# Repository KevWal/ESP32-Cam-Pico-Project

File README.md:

ESP32 Camera Tracker
Written to run on ESP32-Cam board + Lora + GPS

Original code by mkshrps - https://github.com/mkshrps/espcam
Some other ideas from Stuart - https://stuartsprojects.github.io/2020/08/27/ESP32CAM-TrackerAddOn-Board.html

1. Transmits jpg data over lora using SSDV protocol;
2. Interleaves GPS using UKHAS protocol packets;
3. Compatible with PITS LoRa-Gateway receiver.

ESP32-CAM board does not include lora device or GPS device which need to be connected.

Program through the U0R and U0T pins (serial pins) with GPIO0 connected to Gnd.
Debugging output is also on the U0R and U0T pins.

Weights
------
12.4g - Tracker inc 180deg Camera, guitar wire GPS & LoRa Aerial<br>
25g - 3 x AAA soldered together with wire - lasted 14 hours in freezer<br>
21g - 2 x AAA in holder with wire<br>
40g - 2 x AA in holder with wire<br>
14g - 450Ma LiPo<br>

LiPo Version, 26.5g total weight:<br>
1 x Qualtex, 72Ltr Helium, 10g free lift, 0.120m3 unstretched volume, 6,400m burst, 1.7m/sec ascent, 60 mins to burst<br>
2 x Qualtex, 58Ltr Helium each, 10g free lift each, 0.120m3 unstretched volume, 8,400m burst, 1.9m/sec ascent, 75 mins to burst<br>

AA Version, 52.5g total weight:<br>
1 x 100g Pawan, 200ltr Helium, 50g free lift, 20,325m burst, 2.9m/sec ascent, 117mins to burst

AAA Version, 12.5g + 25g = 38g total weight:<br>
1 x Qualtex, 70Ltr Helium, 10g free lift, 0.120m3 unstretched volume, 4,900m burst, 1.7m/sec ascent, 48 mins to burst<br>
2 x Qualtex, 62Ltr Helium each, 10g free lift each, 0.120m3 unstretched volume, 7,500m burst, 1.9m/sec ascent, 65 mins to burst<br>
2 x Chineese, 58Ltr Helium each, 6g free lift each, 0.120m3 unstretched volume, 7,640m burst, 1.9m/sec ascent, 65 mins to float!  42g / 2 = 21g each + 6g = 27g each

Buck version intended for LiPo but used for 3 x AAA

PCB
---

The PCB is designed with many options, mainly around power.  The board is designed to be powered by 2 x AAA or a 3.7v Lipo.  With 2 x AAA I found it needs a boost converter if using the ATGM GPS.  With 1 x 3.7v Lipo I recomend using the buck convertor.  You could use the 3.3v limiting effect of the Boost regulator, but as it is a charge doubler style is uses more current from the battery.

*Flying showed 3 x AAA with a buck convertor is a good option.*

GPS
---
Expects a NMEA GPS, tested with ATGM and UBLOX MAX GPS's

Lora
----
PCB is based on a Dorji DRF1278F LORA module.

Code should support any of the LORA modules listed here:
https://github.com/sandeepmistry/arduino-LoRa

Cameras
-------
Tested with various view angle versions of the OV2640.  This is the standard ESP32 camera.

Some research on other options below.

OV2640 - 1/4" color CMOS UXGA (1600x1200) 2 megapixel image sensor
Used XGA = 1024x768 or VGA = 640x480
https://www.uctronics.com/download/cam_module/OV2640DS.pdf

OV3660 - 3 megapixels
Supports up to FRAMESIZE_QXGA (2048x1536)
https://github.com/espressif/esp32-camera/files/3783752/OV3660_CSP3_DS_1.3_sida.pdf

OV5640 - 1/4" color CMOS QSXGA 5 megapixel image sensor
Supports up to FRAMESIZE_QSXGA (2560x1920)
https://www.uctronics.com/download/Image_Sensor/OV5640_CSP3_DS.pdf

OV7670 - 0.3Mp
Not reasearched due only 0.3Mp!

OV7725 - 
Supports up to FRAMESIZE_VGA (640x480), doesnt support JPEG

OV9650 - Not supported in main repo.
https://www.uctronics.com/index.php/ov9650-13-mega-pixels-camera-module-p-817l.html

NT99141
Supports QVGA (320x240 xskip or crop), VGA(640x480 xskip or crop) and HD (1280x720)

https://github.com/espressif/esp32-camera/tree/master/sensors
Included on github latest:
	#define OV2640_PID     (0x26)
	#define OV3660_PID     (0x36)
	#define OV5640_PID     (0x56)
	#define OV7670_PID     (0x76)
	#define OV7725_PID     (0x77)
	#define OV9650_PID     (0x96)
	#define NT99141_PID     (0x14)

Included in esp32 v1.04:
	#define OV2640_PID     (0x26)
	#define OV3660_PID     (0x36)
	#define OV7725_PID     (0x77)
	#define OV9650_PID     (0x96)

ESP32 Cam module
----------------
https://randomnerdtutorials.com/esp32-cam-ai-thinker-pinout/<br>
https://docs.ai-thinker.com/esp32-cam<br>
https://docs.ai-thinker.com/_media/esp32/docs/esp32_cam_sch.pdf<br>
https://www.espressif.com/sites/default/files/documentation/esp32_technical_reference_manual_en.pdf<br>
https://github.com/espressif/esptool/wiki/ESP32-Boot-Mode-Selection

GPIO32 controls camera power, but if you power the camera down I cant seem to re-initialise it without a reboot (which is now done through a deep sleep reboot)

Arduino IDE
-----------
I added a custom board definition for esp32camkw.upload.speed=921600 to speed uploads.
C:\Users\WALTONK\AppData\Local\Arduino15\packages\esp32\hardware\esp32\1.0.4

Simple Build Notes  - 3 x AA/AAA option
---------------------------------------
Batteries - 3 x AA/AAA = 4.8v down to 2.4v

Reg - MCP170333MB SOT89 or similar<br>
Reg - Add C8, C10, C11 & C12 capacitors

GPS - Tested with ATGM or UBlox Max 3.3v GPS chips<br>
GPS - Add GPS Ferrites and capacitors

Tx - Add Dorji DRF1278F module<br>
Tx - Add R1, C7, C3 and C6<br>
Tx - Set jumper to 3.3v

ESP32 - Add C2, C5, R5 & R6<br>
ESP32 - Remove ESP32 Regulator and Flash transistor<br>
ESP32 - Add ESP32 Camera module to PCB

GPS Antenna - Add chip antenna or 46mm wire (total length)<br>
LoRa Antenna - Add 185mm wire (total length)

Lora Mode
---------
Code setup for:
	Implicit Header (LoRa.beginPacket(1))
	SpreadingFactor(6);
    SignalBandwidth(20.8E3);
    ErrorCodingRate4(5);
    SyncWord(0x12);
    enableCrc();
= Dave Akerman PITS mode 1
https://github.com/PiInTheSky/lora-gateway

Power Consumption
------------------
ESP32 Cam module with regulator removed and flash LED transistor removed<br>
	44ma - Default frequency<br>
	14ma - Reduce to 20Mhz<br>
	14ma - Turn off BT & WIFI<br>
	16ma - Post SPI / Lora Setup<br>
	42ma - Camera setup<br>
	38ma - Disable camera XCLK<br>
	15ma - Turn off camera
	
Board Power Consumption by Frequency, with Lora, GPS and Camera attached but not initialised
	160Mhz, 55ma, 80Mhz, 48ma
	40Mhz, 38ma, 30Mhz, 38ma
	20Mhz, 36ma, 10Mhz, 35ma
	8Mhz, 34ma, 4Mhz, 34ma
	2Mhz, 34ma, 1Mhz, 34ma

ToDo
----
See if we can get Lora and SD Card working together, event though they share pins.  
Stuart did here, but didnt send images: 
https://stuartsprojects.github.io/2020/08/07/ESP32CAM-as-a-Balloon-Tracker-Really!-Copy.html
https://stuartsprojects.github.io/2020/08/27/ESP32CAM-TrackerAddOn-Board.html

Send packets multiple times or auto request resends?

RTTY Code
	Lora library currently in use doesn't appear to have RTTY mode options
	https://github.com/sandeepmistry/arduino-LoRa/blob/master/src/LoRa.cpp
	PITS FSK / RTTY mode details here:
		https://github.com/PiInTheSky/pits/commit/30943ab8ea988695e4e158648f1855fd9fa906bd
		http://www.daveakerman.com/?p=2350
	Stuarts RTTY option here:
		https://github.com/StuartsProjects/Tracker-Library/blob/master/FSK_RTTY2.h
		https://github.com/StuartsProjects/Tracker-Library/blob/master/FSK_RTTY3.h

Add Lora calling frequency tx.

Add use of HabPack binary protocol

Report gps signal quality?
	Base on https://github.com/mikalhart/TinyGPSPlus/blob/master/examples/SatelliteTracker/SatelliteTracker.ino

Record Voltage when taking a picture and send it next telem packet.

PCB
---
Move reset switch hole to be slightly more aligned

Thinner middle pad for buck reg to allow different footprint

Vsupply resister divider on another adc pin too, no solder jumper neeeded.

Increase PCB string holes size, and 4 corner holes to allow vertical down suspension

Lengthen PCB

Different boost converter - current uses lots of current and can't supply enough output current when batteries weak.

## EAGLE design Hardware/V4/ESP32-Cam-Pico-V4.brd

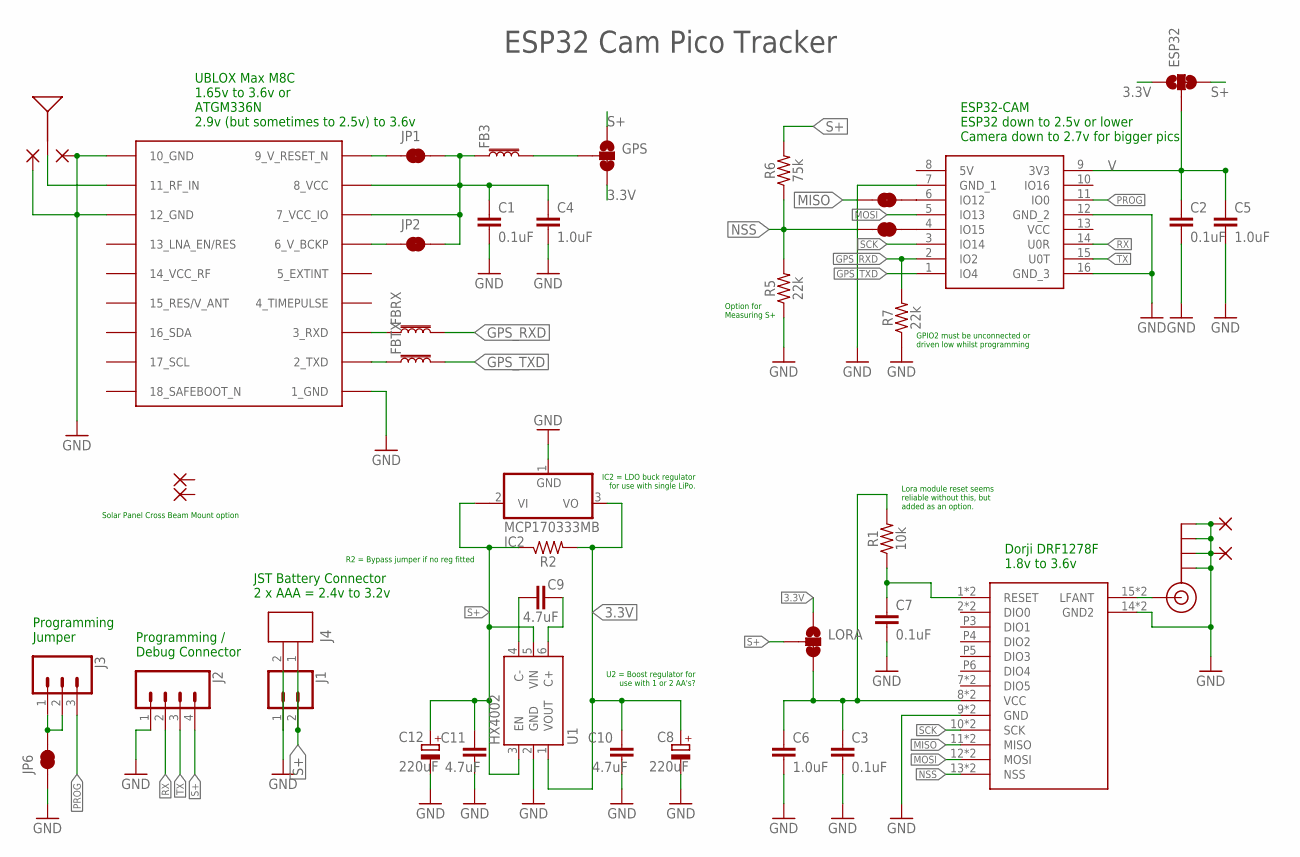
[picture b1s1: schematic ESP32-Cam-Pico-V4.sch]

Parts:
C1, C2, C3, C7: 0.1uF; 0402
C4, C5, C6: 1.0uF; 0402
C8, C12: 220uF; SMC_C
C9, C10, C11: 4.7uF; 0402
ESP32: JUMPER-SMT_3_1-NC_TRACE_SILK; SMT-JUMPER_3_1-NC_TRACE_SILK
FB3: FERRITE_BEAD-120_OHM-0402; 0402
FBRX: FERRITE_BEAD-120_OHM-0402; 0402
FBTX: FERRITE_BEAD-120_OHM-0402; 0402
GPS: JUMPER-SMT_3_1-NC_TRACE_SILK; SMT-JUMPER_3_1-NC_TRACE_SILK
IC1: ESP32-CAM; ESP32CAM
IC2: MCP170333MB; SOT89
J1: CONN_02JST-PTH-2-KIT; JST-2-PTH-KIT
J2: CONN_04LOCK; 1X04_LOCK
J3: CONN_03LOCK; 1X03_LOCK
J4: JST_ZH_2PIN
J$1: SMA_EDGE; SMA-EDGE
JP1, JP2, JP6, JP9, JP10: JUMPER-SMT_2_NC_TRACE_NO-SILK; SMT-JUMPER_2_NC_TRACE_NO-SILK
LORA: JUMPER-SMT_3_1-NC_TRACE_SILK; SMT-JUMPER_3_1-NC_TRACE_SILK
PAD1, PAD2, PAD3, PAD4: 1,6/0,8
PAD5, PAD6: SMD2; SMD1,27-2,54
R1: 10k; 0402
R2: 0k; 0402
R5, R7: 22k; 0402
R6: 75k; 0402
U1: HX4002; SOT23-6
U$1: MAX-M8
U$2: 1.575GHz; ANT-GPS-2X7MM
U$3: DRF1278F_2LESS_PINS; DRF1278F_2_LESS_PINS

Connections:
3.3V: C8.+, C10.1, ESP32.1, GPS.3, IC2.3 (VO), LORA.1, R2.2, U1.1 (VOUT)
ANT: J$1.SIG (SIGNAL), U$3.15 (LFANT), U$3.P15 (LFANT)
GND: C1.2, C2.2, C3.2, C4.2, C5.2, C6.2, C7.2, C8.-, C10.2, C11.2, C12.-, IC1.7 (GND_1), IC1.12 (GND_2), IC1.16 (GND_3), IC2.1 (GND), J1.1, J2.1, J4.2, J$1.GND@0 (GND), J$1.GND@1 (GND), J$1.GND@2 (GND), J$1.GND@3 (GND), JP6.1, PAD1.1, PAD2.1, PAD3.1, PAD4.1, R5.1, R7.1, U1.2 (GND), U$1.1_GND, U$1.10_GND, U$1.12_GND, U$3.9 (GND), U$3.14 (GND2), U$3.P9 (GND), U$3.P14 (GND2); also elsewhere on the board
GPS_RXD: FBRX.2, IC1.2 (IO2), R7.2
GPS_TXD: FBTX.2, IC1.1 (IO4)
MISO: JP9.1, U$3.11 (MISO), U$3.P11 (MISO)
MOSI: IC1.5 (IO13), U$3.12 (MOSI), U$3.P12 (MOSI)
unnamed: U$1.11_RF_IN, U$2.1
unnamed: FBRX.1, U$1.3_RXD
unnamed: FBTX.1, U$1.2_TXD
unnamed: JP1.1, U$1.9_RESET_N (9_V_RESET_N)
unnamed: JP2.1, U$1.6_V_BCKP
unnamed: C7.1, R1.1, U$3.1 (RESET), U$3.P1 (RESET)
unnamed: FB3.2, GPS.2
unnamed: C1.1, C4.1, FB3.1, JP1.2, JP2.2, U$1.7_VCC_IO, U$1.8_VCC
unnamed: C9.2, U1.4 (C-)
unnamed: J3.1, J3.2, JP6.2
unnamed: C9.1, U1.6 (C+)
unnamed: IC1.6 (IO12), JP9.2
unnamed: IC1.4 (IO15), JP10.2
NSS: JP10.1, R5.2, R6.1, U$3.13 (NSS), U$3.P13 (NSS)
PROG: IC1.11 (IO0), J3.3
RX: IC1.14 (U0R), J2.2
S+: C3.1, C6.1, C11.1, C12.+, ESP32.3, GPS.1, IC2.2@1 (VI1), J1.2, J2.4, J4.1, LORA.2, LORA.3, R1.2, R2.1, R6.2, U1.3 (EN), U1.5 (VIN), U$3.8 (VCC), U$3.P8 (VCC); also elsewhere on the board
SCK: IC1.3 (IO14), U$3.10 (SCK), U$3.P10 (SCK)
TX: IC1.15 (U0T), J2.3
V: C2.1, C5.1, ESP32.2, IC1.9 (3V3)

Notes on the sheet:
JST Battery Connector 2 x AAA = 2.4v to 3.2v
Programming / Debug Connector
Programming Jumper
UBLOX Max M8C 1.65v to 3.6v or ATGM336N 2.9v (but sometimes to 2.5v) to 3.6v
Dorji DRF1278F 1.8v to 3.6v
ESP32-CAM ESP32 down to 2.5v or lower Camera down to 2.7v for bigger pics
ESP32 Cam Pico Tracker
Lora module reset seems reliable without this, but added as an option.
R2 = Bypass jumper if no reg fitted
Option for Measuring S+
IC2 = LDO buck regulator for use with single LiPo.
U2 = Boost regulator for use with 1 or 2 AA's?
GPIO2 must be unconnected or driven low whilst programming
Solar Panel Cross Beam Mount option

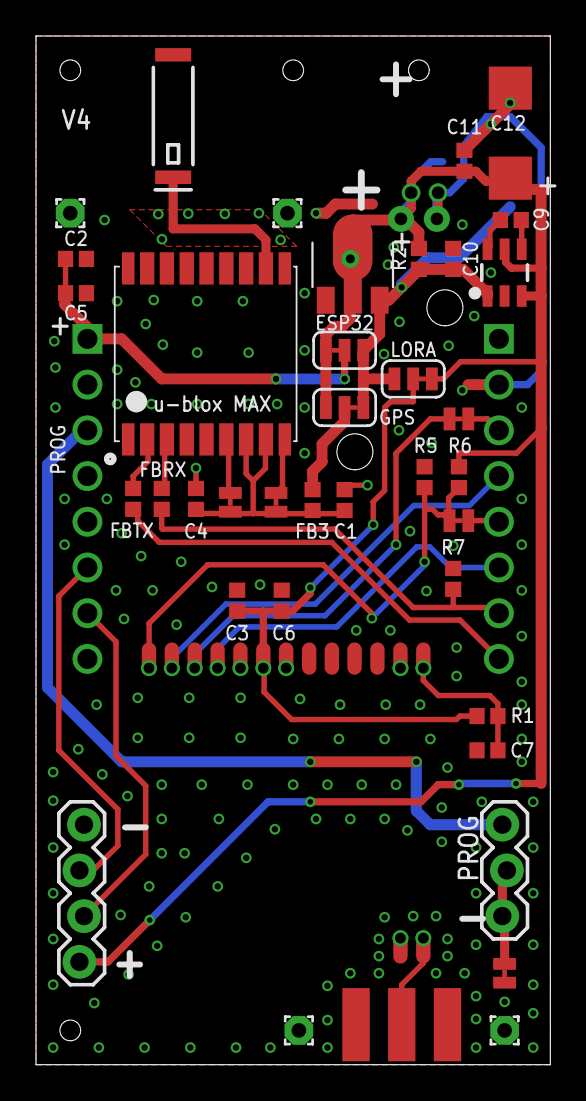
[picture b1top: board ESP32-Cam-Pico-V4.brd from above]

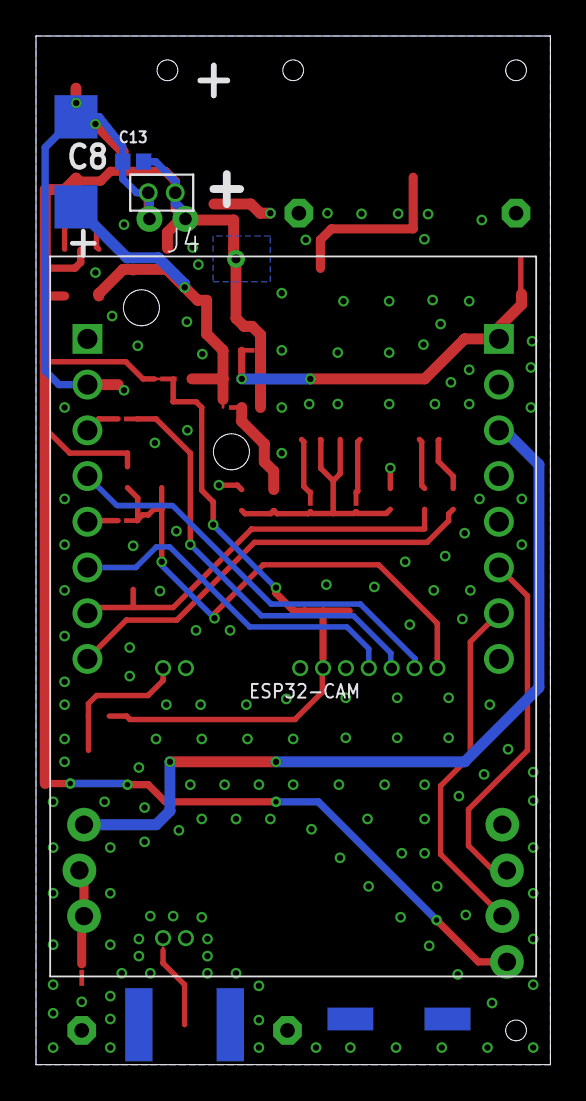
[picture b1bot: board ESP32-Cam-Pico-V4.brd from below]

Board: 2 copper layers, 28.6 x 57.1 mm, 46 parts (7 on the bottom side), 27 nets.

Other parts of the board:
C13: 4.7uF; 0402

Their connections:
GND: C13.2; also elsewhere on the board
S+: C13.1; also elsewhere on the board

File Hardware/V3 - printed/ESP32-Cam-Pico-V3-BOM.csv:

"Qty";"Value";"Device";"Package";"Parts";"Description";"ARROW_PART_NUMBER";"ARROW_PRICE-STOCK";"DESCRIPTION";"HEIGHT";"MANUFACTURER_NAME";"MANUFACTURER_PART_NUMBER";"MFG_PART";"MOUSER_PART_NUMBER";"MOUSER_PRICE-STOCK";"POPULARITY";"PROD_ID";"SF_ID";"SPICEPREFIX";"VALUE";
"4";"";"1,6/0,8";"1,6/0,8";"PAD1, PAD2, PAD3, PAD4";"THROUGH-HOLE PAD";"";"";"";"";"";"";"";"";"";"15";"";"";"";"";
"1";"";"CONN_02JST-PTH-2-KIT";"JST-2-PTH-KIT";"J1";"Multi connection point. Often used as Generic Header-pin footprint for 0.1 inch spaced/style header connections";"";"";"";"";"";"";"";"";"";"";"";"";"";"";
"1";"";"CONN_02LOCK";"1X02_LOCK";"J3";"Multi connection point. Often used as Generic Header-pin footprint for 0.1 inch spaced/style header connections";"";"";"";"";"";"";"";"";"";"";"";"";"";"";
"1";"";"CONN_04LOCK";"1X04_LOCK";"J2";"Multi connection point. Often used as Generic Header-pin footprint for 0.1 inch spaced/style header connections";"";"";"";"";"";"";"";"";"";"";"CONN-09696";"";"";"";
"2";"";"SMD2";"SMD1,27-2,54";"PAD5, PAD6";"SMD PAD";"";"";"";"";"";"";"";"";"";"15";"";"";"";"";
"4";"0.1uF";"0.1UF-0402-6.3V-10%-X7R";"0402";"C1, C2, C3, C7";"0.1µF ceramic capacitors";"";"";"";"";"";"";"";"";"";"";"CAP-14993";"";"";"0.1uF";
"1";"0k";"10KOHM-0402-1/16W-1%";"0402";"R2";"10kΩ resistor";"";"";"";"";"";"";"";"";"";"";"RES-14241";"";"";"10k";
"3";"1.0uF";"1.0UF-0402-16V-10%";"0402";"C4, C5, C6";"1µF ceramic capacitors";"";"";"";"";"";"";"";"";"";"";"CAP-12417";"";"";"1.0uF";
"1";"1.575GHz";"ANTENNAGPS-2X7MM";"ANT-GPS-2X7MM";"U$2";"Single-ended Antennae";"";"";"";"";"";"";"";"";"";"";"ANT-09087";"GPS-09131";"";"1.575GHz";
"4";"10k";"10KOHM-0402-1/16W-1%";"0402";"R1, R5, R6, R7";"10kΩ resistor";"";"";"";"";"";"";"";"";"";"";"RES-14241";"";"";"10k";
"2";"220uF";"CPOL-EUSMCC";"SMC_C";"C8, C12";"POLARIZED CAPACITOR, European symbol";"";"";"";"";"";"";"";"";"";"4";"";"";"C";"";
"3";"4.7uF";"1.0UF-0402-16V-10%";"0402";"C9, C10, C11";"1µF ceramic capacitors";"";"";"";"";"";"";"";"";"";"";"CAP-12417";"";"";"1.0uF";
"1";"DRF1278F_2LESS_PINS";"DRF1278F_2LESS_PINS";"DRF1278F_2_LESS_PINS";"U$3";"";"";"";"";"";"";"";"";"";"";"";"";"";"";"";
"1";"ESP32-CAM";"ESP32-CAM";"ESP32CAM";"IC1";"Modules PCBA Module RoHS";"";"";"Modules PCBA Module RoHS";"5mm";"Ai-Thinker";"ESP32-CAM";"";"";"";"";"";"";"";"";
"3";"FERRITE_BEAD-120_OHM-0402";"FERRITE_BEAD-120_OHM-0402";"0402";"FB3, FBRX, FBTX";"Ferrite Bead (blocks, cores, rings, chokes, etc.)";"";"";"";"";"";"";"BLM15HB121SN1D";"";"";"";"NDUC-14206";"";"";"";
"1";"HX4002";"CE021SOT-23";"SOT23-6";"U1";"CE021";"";"";"";"";"";"";"";"";"";"";"";"";"";"HX4002";
"5";"JUMPER-SMT_2_NC_TRACE_NO-SILK";"JUMPER-SMT_2_NC_TRACE_NO-SILK";"SMT-JUMPER_2_NC_TRACE_NO-SILK";"JP1, JP2, JP6, JP9, JP10";"Normally closed trace jumper";"";"";"";"";"";"";"";"";"";"";"";"";"";"";
"3";"JUMPER-SMT_3_1-NC_TRACE_SILK";"JUMPER-SMT_3_1-NC_TRACE_SILK";"SMT-JUMPER_3_1-NC_TRACE_SILK";"ESP32, GPS, LORA";"Normally closed trace jumper (1 of 2 connections)";"";"";"";"";"";"";"";"";"";"";"";"";"";"";
"1";"MAX-M8";"MAX-M8";"MAX-M8";"U$1";"u-blox MAX GNSS module";"";"";"";"";"";"";"";"";"";"";"";"";"";"";
"1";"MCP170333MB";"MCP170333MB";"SOT89";"IC2";"250 mA, 16V, Low Quiescent Current LDO Regulator";"";"";"";"";"";"";"";"";"";"0";"";"";"";"";
"1";"SMA_EDGE";"SMA_EDGE";"SMA-EDGE";"J$1";"SMA Antenna Connector";"";"";"";"";"";"";"";"";"";"";"";"";"";"";

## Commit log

2020-12-08 Commit post first flight
2021-01-18 Pre Flight 2
2021-01-23 Flight 2 done
2021-01-24 jpeg to jpg
2021-02-14 Minor updates
2023-02-17 Moved to own repo
2023-02-17 Moved to new repo

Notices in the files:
parts and their libraries:
SparkFun-Capacitors: Licensing: Creative Commons ShareAlike 4.0 International - https://creativecommons.org/licenses/by-sa/4.0
